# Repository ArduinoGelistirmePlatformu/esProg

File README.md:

# esProg
esProg AVR Programmer V:1.1

Bilgisayar Gerektirmeden AVR Projelerinize HEX Yükleyebilir ve Fuses Ayarlarını Yapabilirsiniz.

ilerleyen Zamanda Microchip Ve Stm Ailesinide eklemeyi Düşünüyorum.

Arduino Geliştirme Platformu: https://www.facebook.com/groups/Arduino.Pic

Video: https://www.youtube.com/watch?v=lhsaVAEl87k&t=31s

Website: https://espprog.blogspot.com/

# Programmer Device Family
 ATtiny13A
 ATtiny24
 ATtiny44
 ATtiny84
 ATtiny25
 ATtiny45
 ATtiny85
 ATtiny2313A
 ATtiny4313
 ATmega8A
 ATmega48PA
 ATmega88PA
 ATmega168PA
 ATmega168V
 ATmega328P
 ATmega328PB
 ATmega328
 ATmega164P
 ATmega324P
 ATmega644P
 ATmega640
 ATmega1280
 ATmega1281
 ATmega2560
 ATmega2561
 At90USB82
 At90USB162
 ATmega8U2
 ATmega16U2
 ATmega32U2
 ATmega16U4
 ATmega32U4
 ATmega1284P
 ATmega1284
 ATmega64rfr2
 ATmega128rfr2
 ATmega256rfr2

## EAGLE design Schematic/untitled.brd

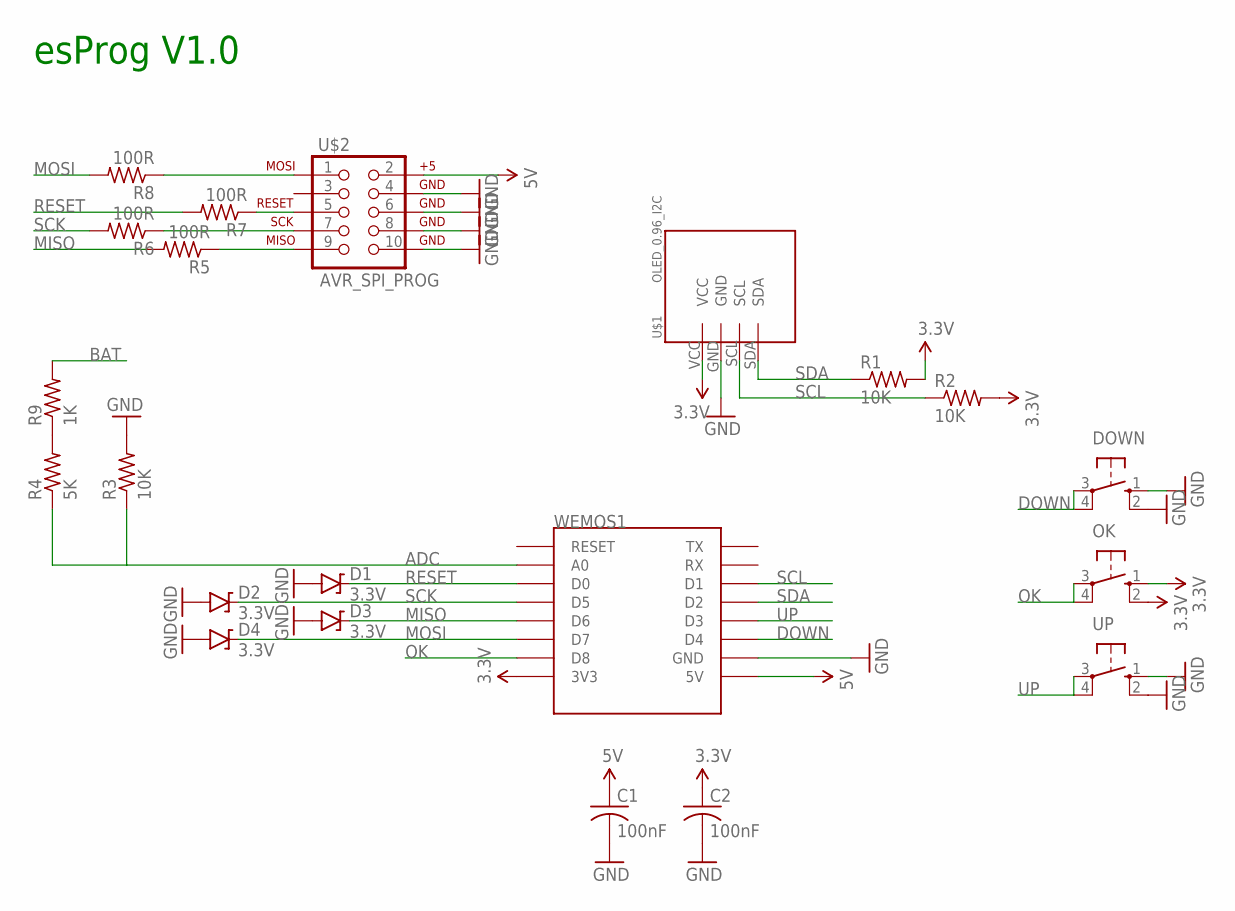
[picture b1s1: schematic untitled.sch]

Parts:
C1, C2: 100nF; C0805K
D1, D2, D3, D4: 3.3V; SOD-323
DOWN: 10-XX; B3F-10XX
OK: 10-XX; B3F-10XX
R1, R2, R3: 10K; R0805
R4: 5K; R0805
R5, R6, R7, R8: 100R; R0805
R9: 1K; R0805
U$1: OLED_0.96_I2C
U$2: AVR_SPI_PROG; AVR_ICSP
UP: 10-XX; B3F-10XX
WEMOS1: WEMOS-D1-MINI

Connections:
3.3V: C2.1, OK.1 (S), OK.2 (S1), R1.2, R2.2, U$1.VCC, WEMOS1.3V3
5V: C1.1, U$2.2, WEMOS1.5V
ADC: R3.1, R4.1, WEMOS1.A0
BAT: R9.2
DOWN: DOWN.3, DOWN.4 (P1), WEMOS1.D4
GND: C1.2, C2.2, D1.A, D2.A, D3.A, D4.A, DOWN.1 (S), DOWN.2 (S1), R3.2, U$1.GND, U$2.4, U$2.6, U$2.8, U$2.10, UP.1 (S), UP.2 (S1), WEMOS1.GND
MISO: D3.C, R5.2, WEMOS1.D6
MOSI: D4.C, R8.2, WEMOS1.D7
unnamed: R8.1, U$2.1
unnamed: R7.1, U$2.5
unnamed: R6.1, U$2.7
unnamed: R5.1, U$2.9
unnamed: R4.2, R9.1
OK: OK.3, OK.4 (P1), WEMOS1.D8
RESET: D1.C, R7.2, WEMOS1.D0
SCK: D2.C, R6.2, WEMOS1.D5
SCL: R2.1, U$1.SCL, WEMOS1.D1
SDA: R1.1, U$1.SDA, WEMOS1.D2
UP: UP.3, UP.4 (P1), WEMOS1.D3

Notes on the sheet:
esProg V1.0

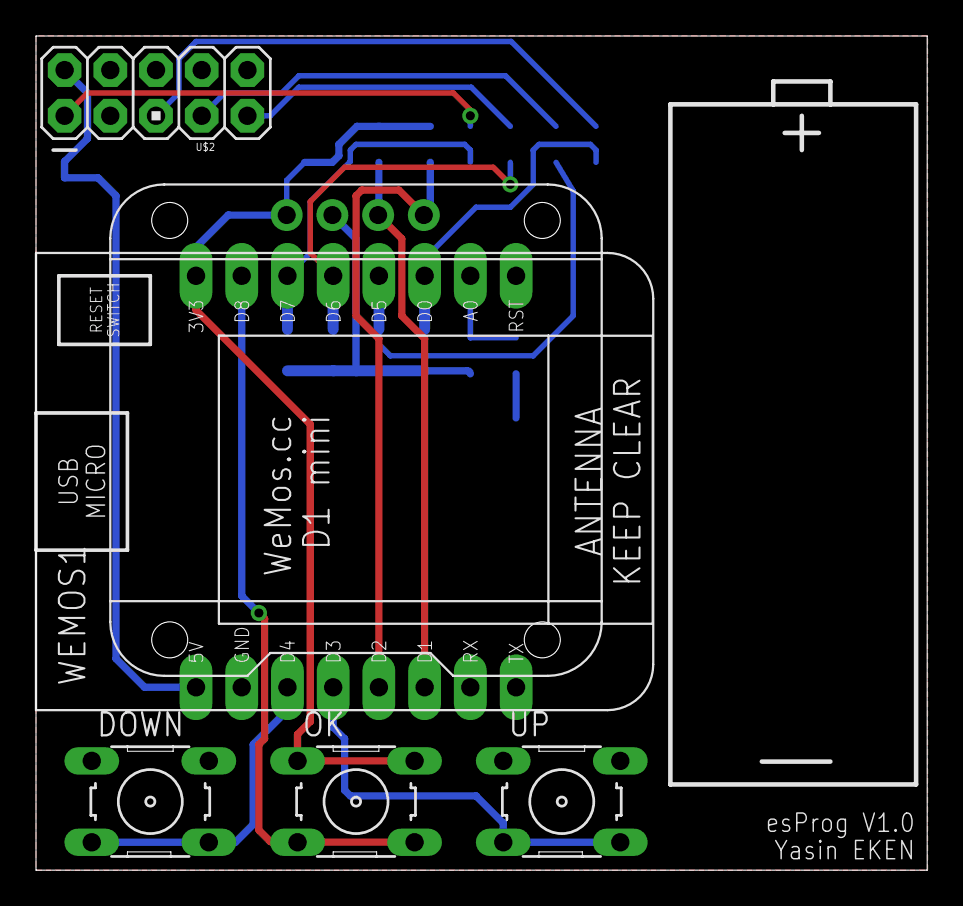
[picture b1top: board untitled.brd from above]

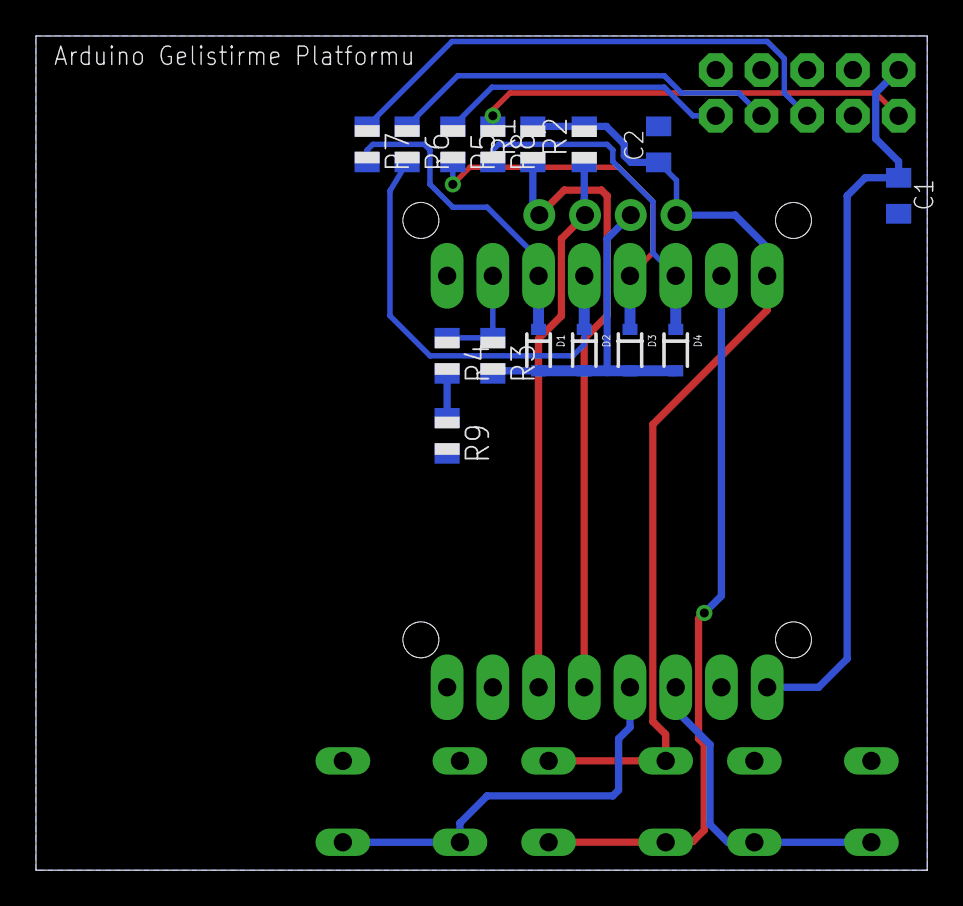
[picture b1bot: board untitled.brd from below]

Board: 2 copper layers, 49.5 x 46.3 mm, 21 parts (15 on the bottom side), 18 nets.

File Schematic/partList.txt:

Partlist

Exported from untitled.sch at 23.09.2019 10:48

EAGLE Version 7.7.0 Copyright (c) 1988-2016 CadSoft

Assembly variant: 

Part     Value          Device          Package       Library                Sheet

C1       100nF          C-USC0805K      C0805K        adafruit               1
C2       100nF          C-USC0805K      C0805K        adafruit               1
D1       3.3V           DIODE-ZENER3.3V SOD-323       SparkFun-DiscreteSemi  1
D2       3.3V           DIODE-ZENER3.3V SOD-323       SparkFun-DiscreteSemi  1
D3       3.3V           DIODE-ZENER3.3V SOD-323       SparkFun-DiscreteSemi  1
D4       3.3V           DIODE-ZENER3.3V SOD-323       SparkFun-DiscreteSemi  1
DOWN                    10-XX           B3F-10XX      switch-omron           1
OK                      10-XX           B3F-10XX      switch-omron           1
R1       10K            R-US_R0805      R0805         adafruit               1
R2       10K            R-US_R0805      R0805         adafruit               1
R3       10K            R-US_R0805      R0805         adafruit               1
R4       6K             R-US_R0805      R0805         adafruit               1
R5       100R           R-US_R0805      R0805         adafruit               1
R6       100R           R-US_R0805      R0805         adafruit               1
R7       100R           R-US_R0805      R0805         adafruit               1
R8       100R           R-US_R0805      R0805         adafruit               1
U$1      OLED_0.96_I2C  OLED_0.96_I2C   OLED_0.96_I2C tft_1.8_1.44_oled_0.96 1
U$2      AVR_SPI_PROG   AVR_SPI_PROG    AVR_ICSP      SparkFun-Connectors    1
UP                      10-XX           B3F-10XX      switch-omron           1
WEMOS1                  WEMOS-D1-MINI   WEMOS-D1-MINI esp8266modules         1

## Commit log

2019-09-16 :octocat: Added .gitattributes & .gitignore files
2019-09-16 esProg AVR Programmer
    esProg AVR Programmer
2019-09-18 spiffs V1.1
    spiffs V1.1
2019-09-19 esProg AVR Programmer V1.1
    esProg AVR Programmer V1.1

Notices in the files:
parts and their libraries:
SparkFun-DiscreteSemi: Licensing: Creative Commons ShareAlike 4.0 International - https://creativecommons.org/licenses/by-sa/4.0
